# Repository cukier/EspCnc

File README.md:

# EspCnc

Controlador ESP32 para uma fresadora CNC 3018/3020/3030-3035, baseado no
firmware [grbl_esp32](https://github.com/bdring/grbl_esp32) (Bart Dring) e no
[esquematico de referencia da buildlog.net](https://www.buildlog.net/blog/wp-content/uploads/2018/07/esp32_test_schem_v1.pdf).

O objetivo e substituir a controladora original da CNC 3035 (tipicamente
baseada em GRBL sobre Arduino/Atmega) por uma placa com ESP32, aproveitando
mais pinos, maior clock, Wi-Fi/Bluetooth e a arquitetura de I/O configuravel
que o grbl_esp32 introduziu.

Este repositorio contem dois projetos independentes:

- [`firmware/`](firmware/) - firmware para o ESP32, em **ESP-IDF** (nao
  Arduino/PlatformIO), inspirado na logica de interpretacao G-code e no
  planejador de movimento do grbl_esp32.
- [`hardware/`](hardware/) - projeto de placa em **KiCad**, com o
  esquematico e PCB da interface entre o ESP32 e os drivers de motor de
  passo, fins-de-curso, spindle/laser e demais perifericos da CNC 3035,
  usando o esquematico da buildlog.net como ponto de partida.
- [`doc/`](doc/) - documentacao de referencia, incluindo o esquematico da
  buildlog.net usado como base do projeto.

## Estrutura

```
EspCnc/
├── firmware/   # Projeto ESP-IDF
├── hardware/   # Projeto KiCad
└── doc/        # Documentacao de referencia (esquematico, etc.)
```

## Firmware (ESP-IDF)

Ver [firmware/README.md](firmware/README.md).

## Hardware (KiCad)

Ver [hardware/README.md](hardware/README.md).

## Referencias

- grbl_esp32 (Bart Dring): https://github.com/bdring/grbl_esp32
- Esquematico ESP32 CNC (buildlog.net): https://www.buildlog.net/blog/wp-content/uploads/2018/07/esp32_test_schem_v1.pdf
- GRBL original: https://github.com/gnea/grbl

## Licenca

Distribuido sob a licenca MIT. Veja [LICENSE](LICENSE).

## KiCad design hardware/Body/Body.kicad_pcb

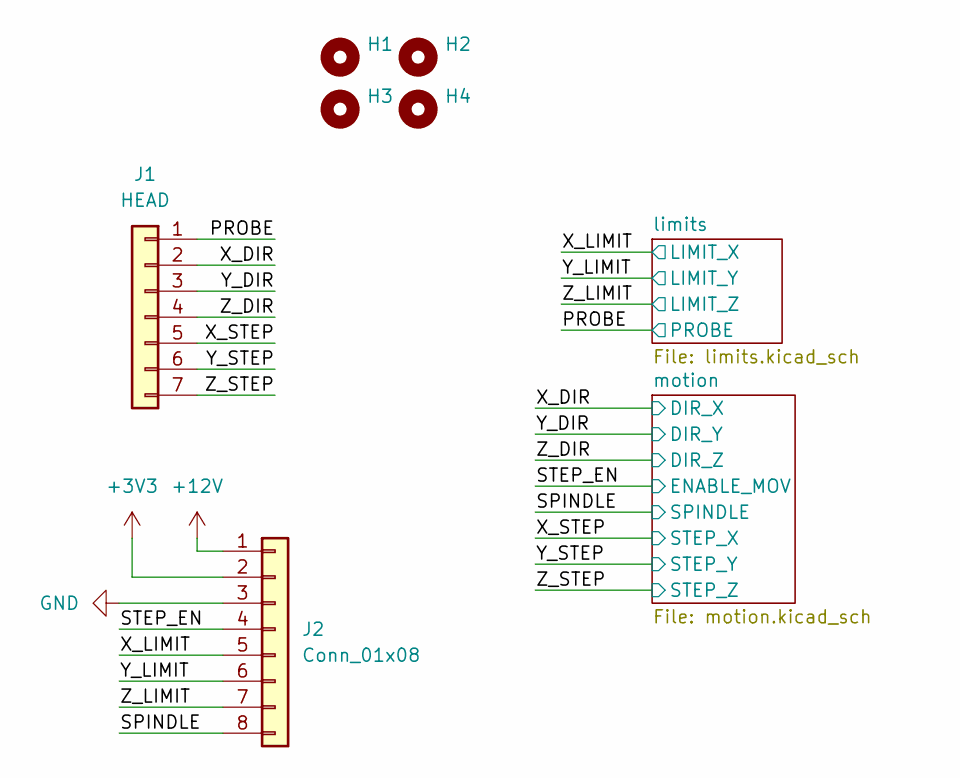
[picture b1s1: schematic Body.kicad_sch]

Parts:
H1, H2, H3, H4: MountingHole; MountingHole_3.5mm
J1: HEAD; PinSocket_1x07_P2.54mm_Vertical
J2: Conn_01x08; PinSocket_1x08_P2.54mm_Vertical

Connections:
+3V3: J2.2; also elsewhere on the board
+12V: J2.1; also elsewhere on the board
/PROBE: J1.1; also elsewhere on the board
/SPINDLE: J2.8; also elsewhere on the board
/STEP_EN: J2.4; also elsewhere on the board
/X_DIR: J1.2; also elsewhere on the board
/X_LIMIT: J2.5; also elsewhere on the board
/X_STEP: J1.5; also elsewhere on the board
/Y_DIR: J1.3; also elsewhere on the board
/Y_LIMIT: J2.6; also elsewhere on the board
/Y_STEP: J1.6; also elsewhere on the board
/Z_DIR: J1.4; also elsewhere on the board
/Z_LIMIT: J2.7; also elsewhere on the board
/Z_STEP: J1.7; also elsewhere on the board
GND: J2.3; also elsewhere on the board

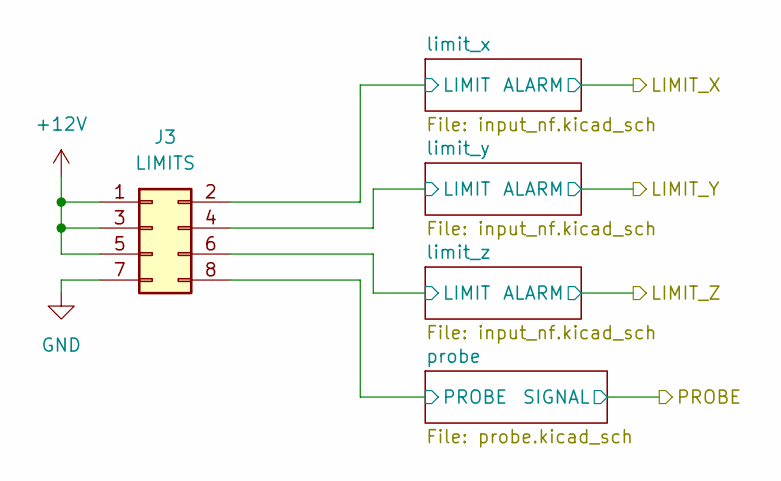
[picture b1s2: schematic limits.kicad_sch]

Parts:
J3: LIMITS; PinHeader_2x04_P2.54mm_Vertical

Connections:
+12V: J3.1, J3.3, J3.5; also elsewhere on the board
/limits/limit_x/LIMIT: J3.2; also elsewhere on the board
/limits/limit_y/LIMIT: J3.4; also elsewhere on the board
/limits/limit_z/LIMIT: J3.6; also elsewhere on the board
/limits/probe/PROBE: J3.8; also elsewhere on the board
GND: J3.7; also elsewhere on the board

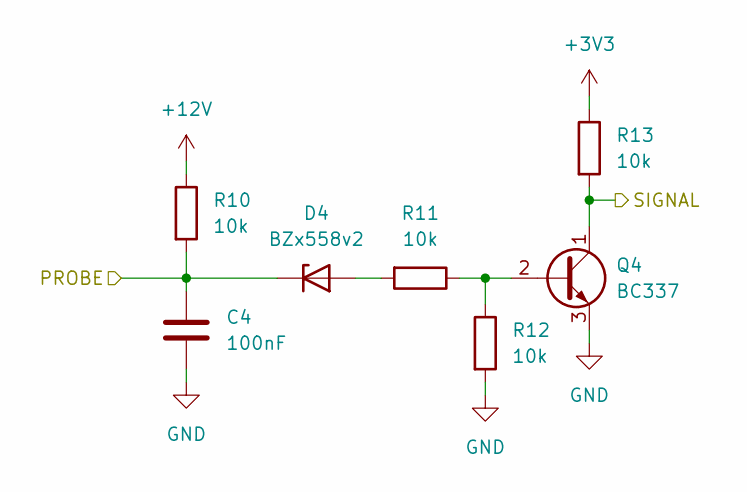
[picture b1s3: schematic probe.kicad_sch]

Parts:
C4: 100nF; C_1206_3216Metric_Pad1.33x1.80mm_HandSolder
D4: BZx558v2; D_MELF_Handsoldering
Q4: BC337; TO-92_Inline_Wide
R10, R11, R12, R13: 10k; R_1206_3216Metric_Pad1.30x1.75mm_HandSolder

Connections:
+3V3: R13.1; also elsewhere on the board
+12V: R10.1; also elsewhere on the board
/PROBE: Q4.1 (C), R13.2; also elsewhere on the board
/limits/probe/PROBE: C4.1, D4.1 (K), R10.2; also elsewhere on the board
GND: C4.2, Q4.3 (E), R12.2; also elsewhere on the board
unnamed: D4.2 (A), R11.2
unnamed: Q4.2 (B), R11.1, R12.1

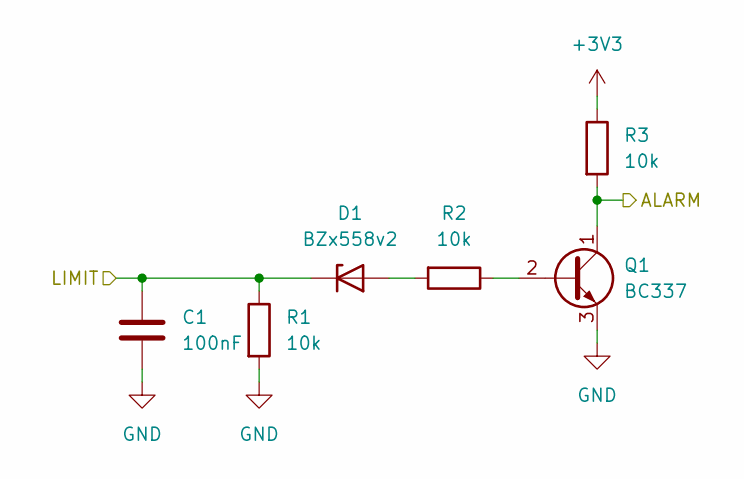
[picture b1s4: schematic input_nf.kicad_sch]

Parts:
C1: 100nF; C_1206_3216Metric_Pad1.33x1.80mm_HandSolder
D1: BZx558v2; D_MELF_Handsoldering
Q1: BC337; TO-92_Inline_Wide
R1, R2, R3: 10k; R_1206_3216Metric_Pad1.30x1.75mm_HandSolder

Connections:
+3V3: R3.1; also elsewhere on the board
/X_LIMIT: Q1.1 (C), R3.2; also elsewhere on the board
/limits/limit_x/LIMIT: C1.1, D1.1 (K), R1.1; also elsewhere on the board
GND: C1.2, Q1.3 (E), R1.2; also elsewhere on the board
unnamed: D1.2 (A), R2.2
unnamed: Q1.2 (B), R2.1

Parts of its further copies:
C2, C3: 100nF; C_1206_3216Metric_Pad1.33x1.80mm_HandSolder
D2, D3: BZx558v2; D_MELF_Handsoldering
Q2, Q3: BC337; TO-92_Inline_Wide
R4, R5, R6, R7, R8, R9: 10k; R_1206_3216Metric_Pad1.30x1.75mm_HandSolder

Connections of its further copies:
+3V3: R6.1, R9.1; also elsewhere on the board
/Y_LIMIT: Q2.1 (C), R6.2; also elsewhere on the board
/Z_LIMIT: Q3.1 (C), R9.2; also elsewhere on the board
/limits/limit_y/LIMIT: C2.1, D2.1 (K), R4.1; also elsewhere on the board
/limits/limit_z/LIMIT: C3.1, D3.1 (K), R7.1; also elsewhere on the board
GND: C2.2, C3.2, Q2.3 (E), Q3.3 (E), R4.2, R7.2; also elsewhere on the board
unnamed: D2.2 (A), R5.2
unnamed: D3.2 (A), R8.2
unnamed: Q2.2 (B), R5.1
unnamed: Q3.2 (B), R8.1

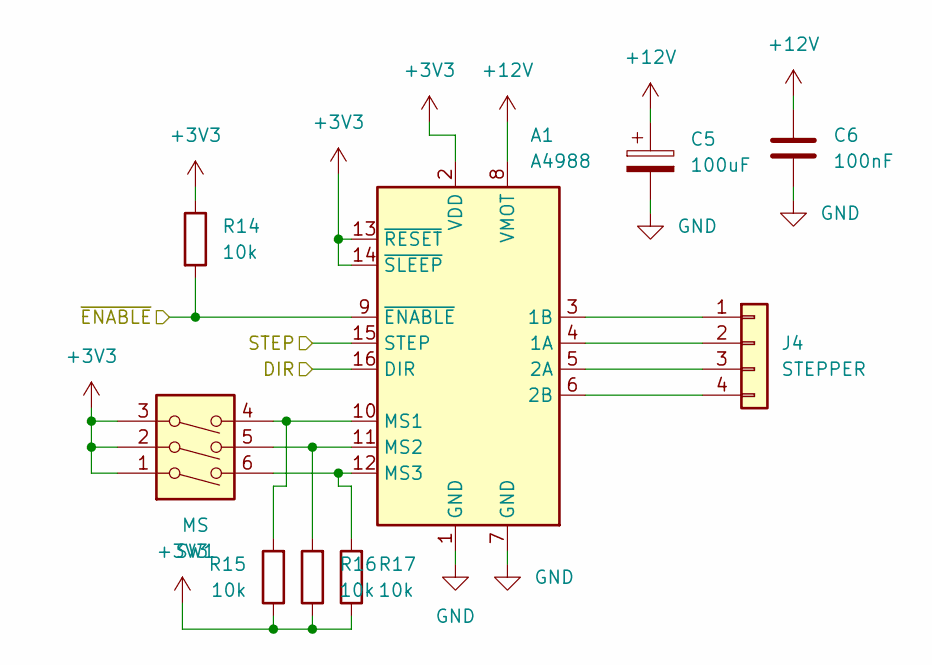
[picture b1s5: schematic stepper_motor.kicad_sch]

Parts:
A1: A4988; Pololu_Breakout-16_15.2x20.3mm
C5: 100uF; CP_Radial_D5.0mm_P2.50mm
C6: 100nF; C_1206_3216Metric_Pad1.33x1.80mm_HandSolder
J4: STEPPER; PinHeader_1x04_P2.54mm_Vertical
R14, R15, R16, R17: 10k; R_1206_3216Metric_Pad1.30x1.75mm_HandSolder
SW1: MS; SW_DIP_SPSTx03_Slide_6.7x9.18mm_W7.62mm_P2.54mm_LowProfile

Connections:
+3V3: A1.2 (VDD), A1.13 (~RESET), A1.14 (~SLEEP), R14.1, R15.1, R16.1, R17.1, SW1.1, SW1.2, SW1.3; also elsewhere on the board
+12V: A1.8 (VMOT), C5.1, C6.1; also elsewhere on the board
/STEP_EN: A1.9 (~ENABLE), R14.2; also elsewhere on the board
/X_DIR: A1.15 (STEP); also elsewhere on the board
/X_STEP: A1.16 (DIR); also elsewhere on the board
GND: A1.1 (GND), A1.7 (GND), C5.2, C6.2; also elsewhere on the board
unnamed: A1.4 (1A), J4.2
unnamed: A1.3 (1B), J4.1
unnamed: A1.5 (2A), J4.3
unnamed: A1.6 (2B), J4.4
unnamed: A1.10 (MS1), R15.2, SW1.4
unnamed: A1.11 (MS2), R16.2, SW1.5
unnamed: A1.12 (MS3), R17.2, SW1.6

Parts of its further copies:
A2, A3: A4988; Pololu_Breakout-16_15.2x20.3mm
C7, C9: 100uF; CP_Radial_D5.0mm_P2.50mm
C8, C10: 100nF; C_1206_3216Metric_Pad1.33x1.80mm_HandSolder
J5, J6: STEPPER; PinHeader_1x04_P2.54mm_Vertical
R18, R19, R20, R21, R22, R23, R24, R25: 10k; R_1206_3216Metric_Pad1.30x1.75mm_HandSolder
SW2, SW3: MS; SW_DIP_SPSTx03_Slide_6.7x9.18mm_W7.62mm_P2.54mm_LowProfile

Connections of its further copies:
+3V3: A2.2 (VDD), A2.13 (~RESET), A2.14 (~SLEEP), A3.2 (VDD), A3.13 (~RESET), A3.14 (~SLEEP), R18.1, R19.1, R20.1, R21.1, R22.1, R23.1, R24.1, R25.1, SW2.1, SW2.2, SW2.3, SW3.1, SW3.2, SW3.3; also elsewhere on the board
+12V: A2.8 (VMOT), A3.8 (VMOT), C7.1, C8.1, C9.1, C10.1; also elsewhere on the board
/STEP_EN: A2.9 (~ENABLE), A3.9 (~ENABLE), R18.2, R22.2; also elsewhere on the board
/Y_DIR: A2.15 (STEP); also elsewhere on the board
/Y_STEP: A2.16 (DIR); also elsewhere on the board
/Z_DIR: A3.15 (STEP); also elsewhere on the board
/Z_STEP: A3.16 (DIR); also elsewhere on the board
GND: A2.1 (GND), A2.7 (GND), A3.1 (GND), A3.7 (GND), C7.2, C8.2, C9.2, C10.2; also elsewhere on the board
unnamed: A2.4 (1A), J5.2
unnamed: A2.3 (1B), J5.1
unnamed: A2.5 (2A), J5.3
unnamed: A2.6 (2B), J5.4
unnamed: A2.10 (MS1), R19.2, SW2.4
unnamed: A2.11 (MS2), R20.2, SW2.5
unnamed: A2.12 (MS3), R21.2, SW2.6
unnamed: A3.4 (1A), J6.2
unnamed: A3.3 (1B), J6.1
unnamed: A3.5 (2A), J6.3
unnamed: A3.6 (2B), J6.4
unnamed: A3.10 (MS1), R23.2, SW3.4
unnamed: A3.11 (MS2), R24.2, SW3.5
unnamed: A3.12 (MS3), R25.2, SW3.6

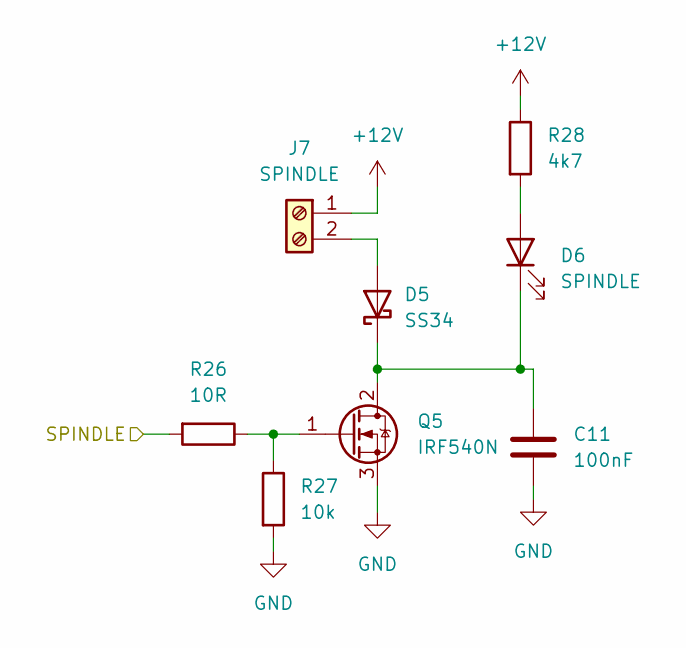
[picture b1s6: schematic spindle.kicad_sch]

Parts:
C11: 100nF; C_1206_3216Metric_Pad1.33x1.80mm_HandSolder
D5: SS34; D_SMA_Handsoldering
D6: SPINDLE; LED_D3.0mm
J7: SPINDLE; TerminalBlock_Phoenix_MKDS-1,5-2-5.08_1x02_P5.08mm_Horizont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
Q5: IRF540N; TO-220-3_Vertical
R26: 10R; R_1206_3216Metric_Pad1.30x1.75mm_HandSolder
R27: 10k; R_1206_3216Metric_Pad1.30x1.75mm_HandSolder
R28: 4k7; R_1206_3216Metric_Pad1.30x1.75mm_HandSolder

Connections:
+12V: J7.1, R28.1; also elsewhere on the board
/SPINDLE: R26.2; also elsewhere on the board
GND: C11.2, Q5.3 (S), R27.2; also elsewhere on the board
unnamed: D5.2 (A), J7.2
unnamed: C11.1, D5.1 (K), D6.1 (K), Q5.2 (D)
unnamed: D6.2 (A), R28.2
unnamed: Q5.1 (G), R26.1, R27.1

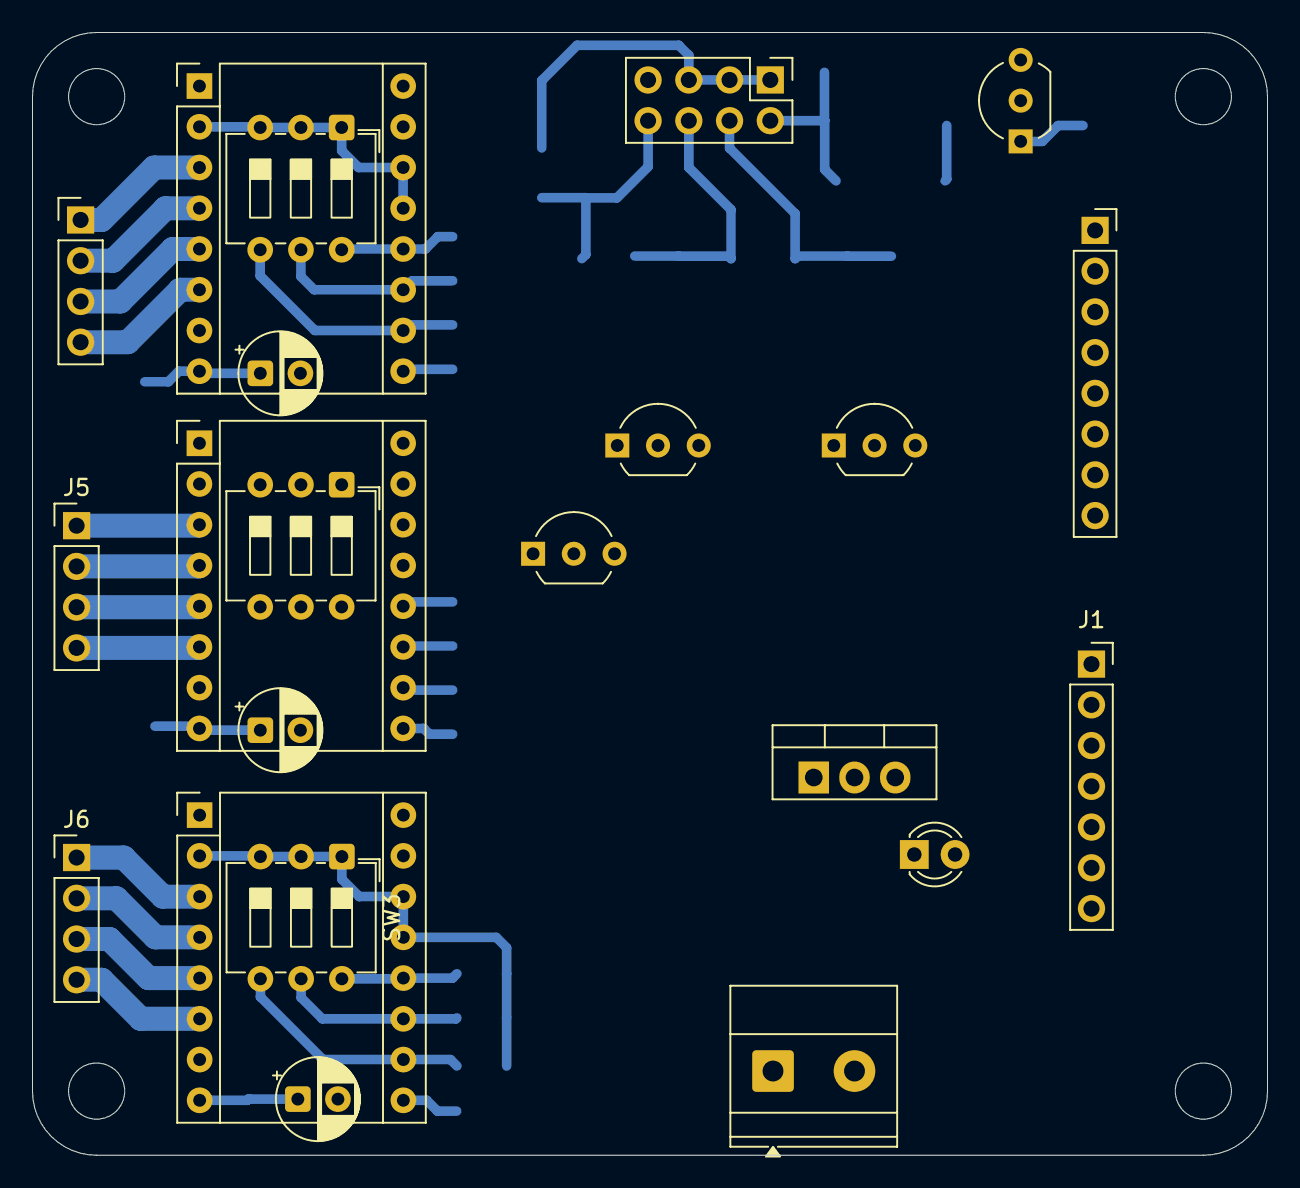
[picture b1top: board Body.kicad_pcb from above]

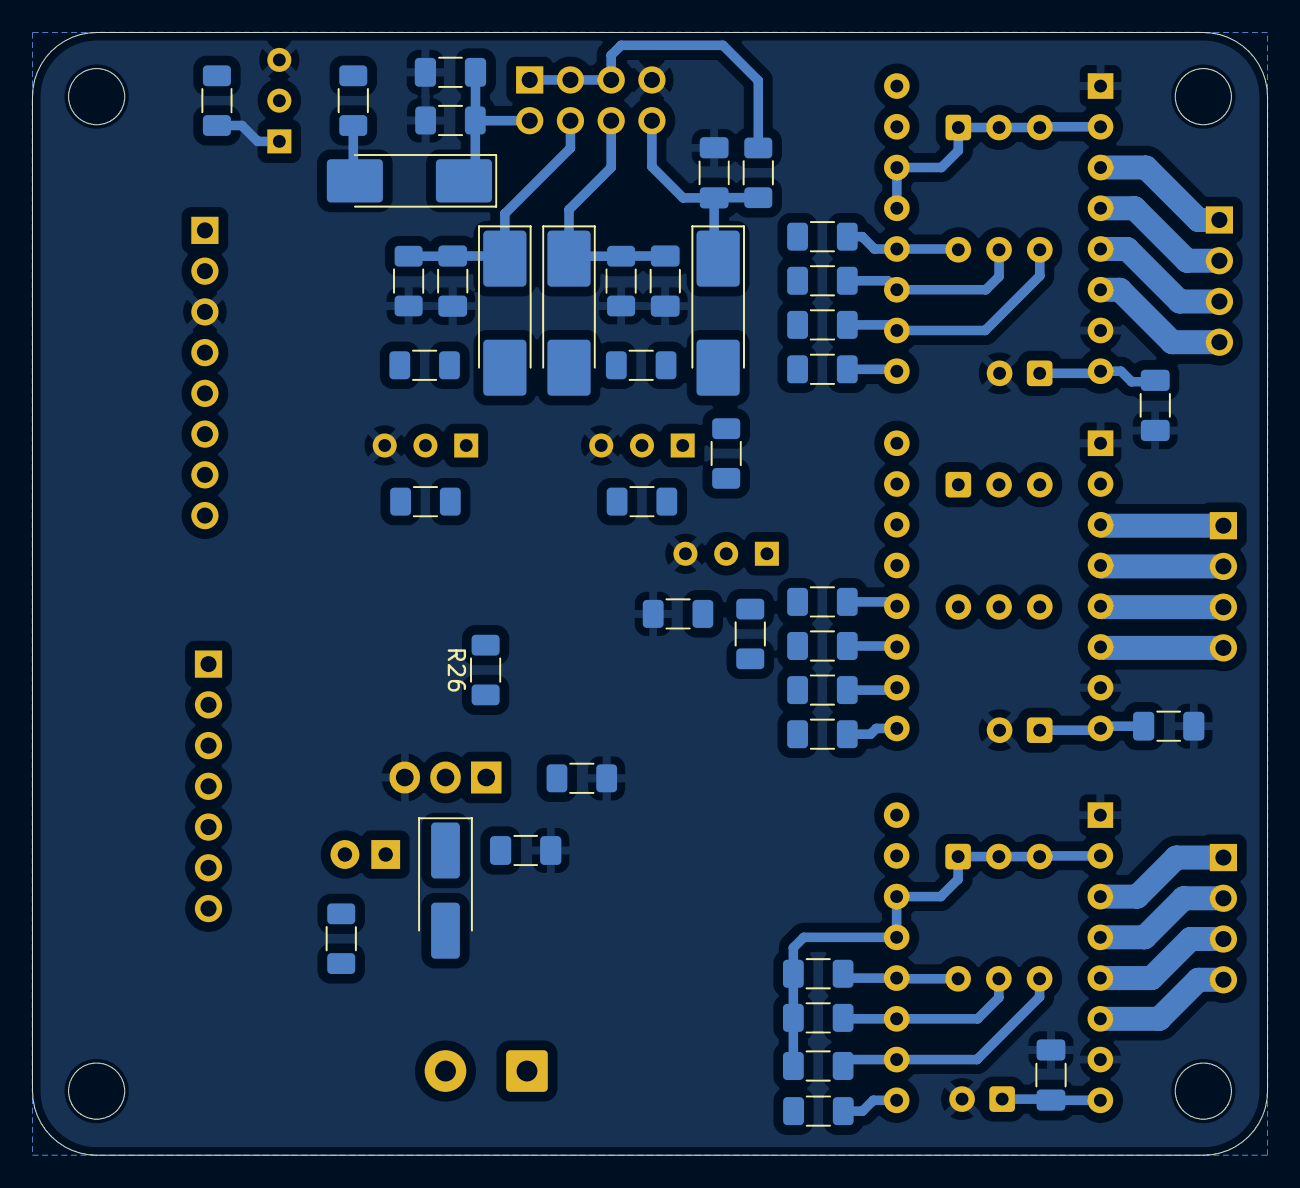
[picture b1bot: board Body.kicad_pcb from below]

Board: 2 copper layers, 77.0 x 70.0 mm, 67 parts (41 on the bottom side), 52 nets.

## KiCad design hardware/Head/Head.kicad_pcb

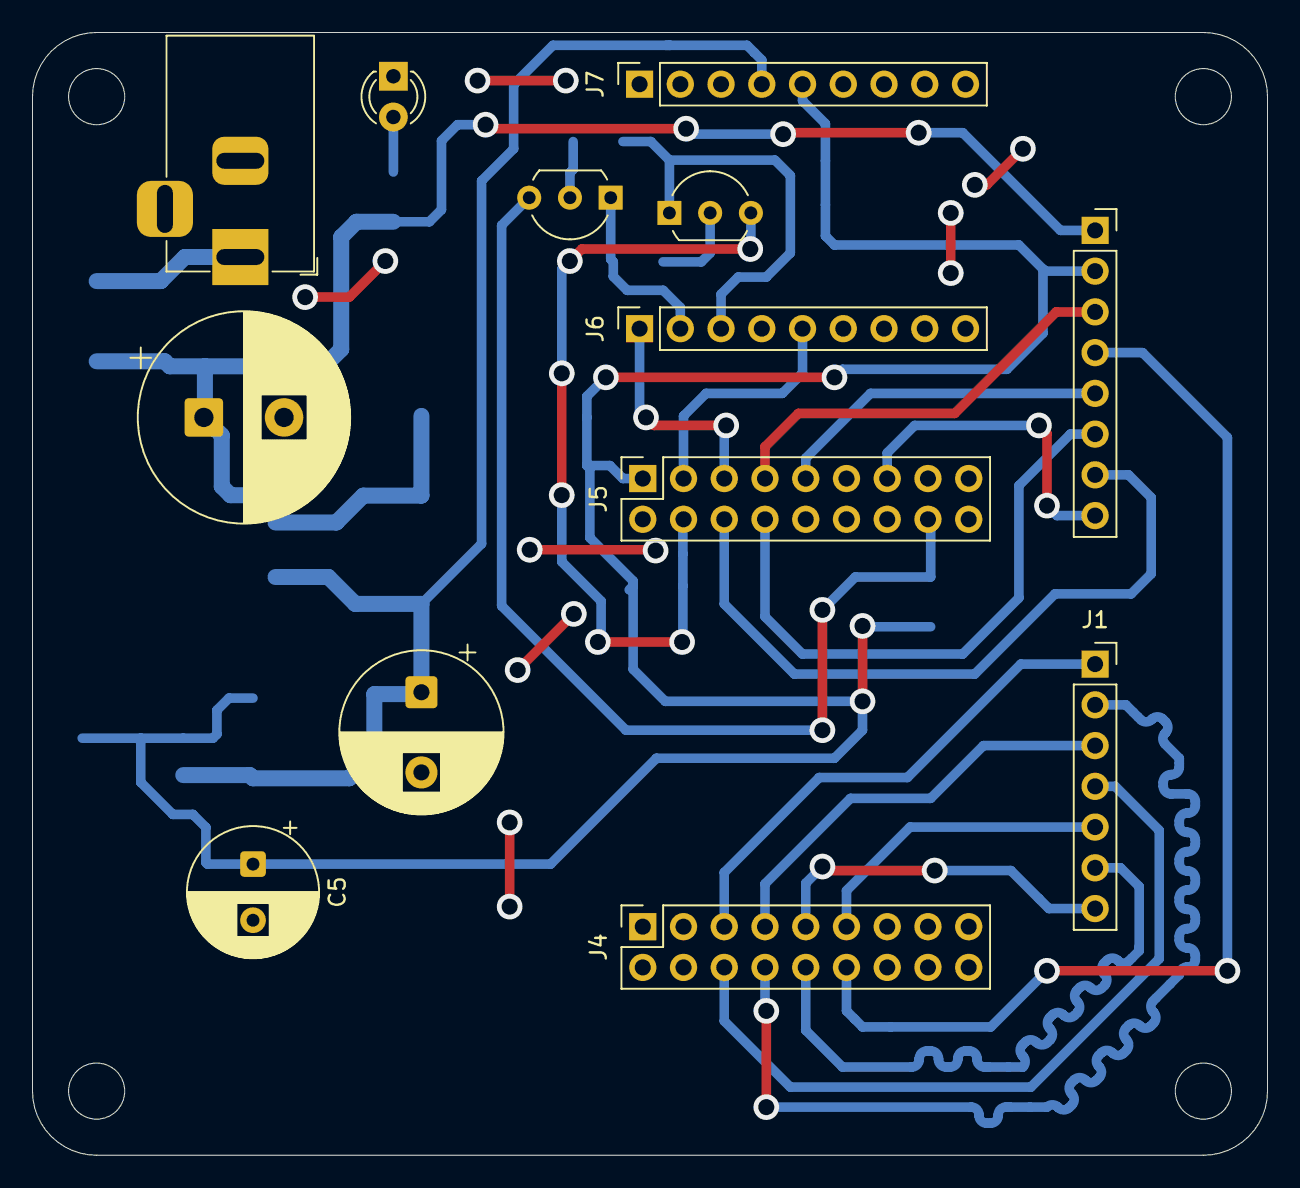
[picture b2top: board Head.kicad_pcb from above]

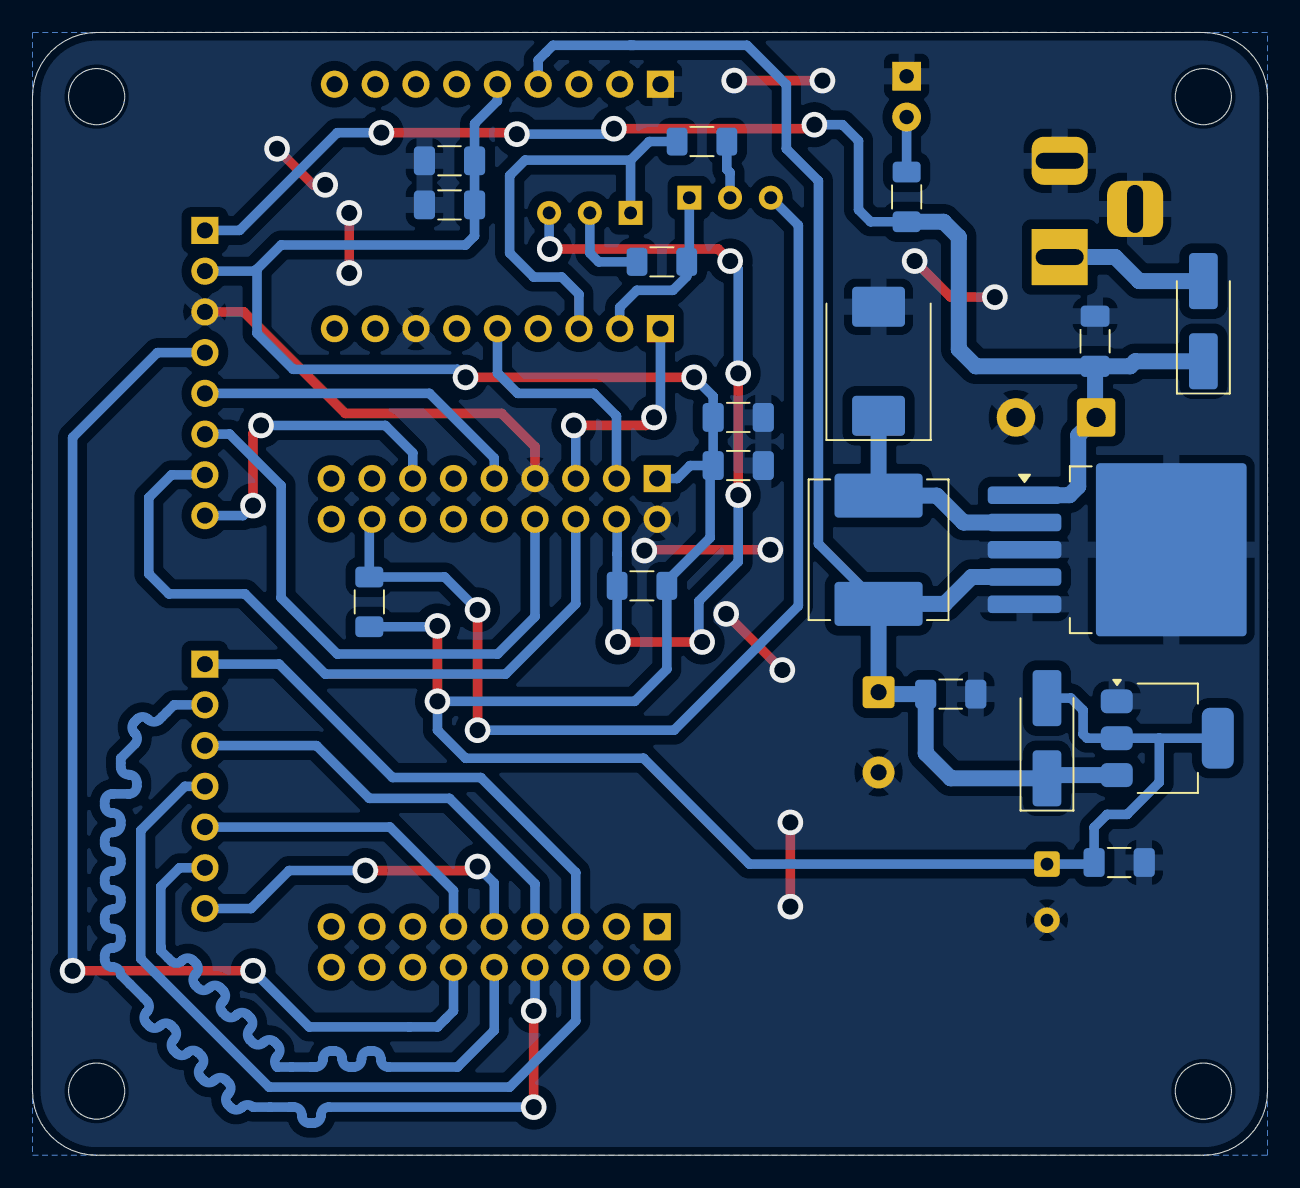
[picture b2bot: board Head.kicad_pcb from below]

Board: 2 copper layers, 77.0 x 70.0 mm, 35 parts (18 on the bottom side), 27 nets.

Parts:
C1: 470uF; CP_Radial_D13.0mm_P5.00mm
C2, C4, C6, C8, C10: 100nF; C_1206_3216Metric_Pad1.33x1.80mm_HandSolder
C3: 1000uF; CP_Radial_D10.0mm_P5.00mm
C5: 22uF; CP_Radial_D8.0mm_P3.50mm
C7, C9: 1uF; C_1206_3216Metric_Pad1.33x1.80mm_HandSolder
D1, D4: US1M; D_SMA_Handsoldering
D2: PWR; LED_D3.0mm
D3: B340; D_SMC
H1, H2, H3, H4: MountingHole; MountingHole_3.5mm
J1: HEAD; PinSocket_1x07_P2.54mm_Vertical
J2: Conn_01x08; PinSocket_1x08_P2.54mm_Vertical
J3: PWR; BarrelJack_Horizontal
J4, J5: ESP_32; PinSocket_2x09_P2.54mm_Vertical
J6: USB_E; PinSocket_1x09_P2.54mm_Vertical
J7: USB_D; PinSocket_1x09_P2.54mm_Vertical
L1: 100uH; L_Changjiang_FXL0840
Q1, Q2: PN2222A; TO-92L_Inline_Wide
R1, R2, R3, R4, R5: 10k; R_1206_3216Metric_Pad1.30x1.75mm_HandSolder
U1: LM2576HVS-5; TO-263-5_TabPin3
U2: AMS1117-3.3; SOT-223-3_TabPin2

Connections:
+3V3: C5.1, C6.1, C7.1, C8.1, C9.1, C10.1, D4.2 (A), J2.2, J5.1, J7.5, R3.2, R5.2, U2.2 (VO)
+5V: C3.1, C4.1, D4.1 (K), J7.4, L1.2, U1.4 (FB), U2.3 (VI)
+12V: C1.1, C2.1, D1.1 (K), J2.1, R1.1, U1.1 (VIN)
/BOOT: J5.16, Q2.3 (C), R5.1
/CH_PU: J5.4, Q1.3 (C), R3.1
/PROBE: J1.1, J4.5
/SPINDLE: J2.8, J5.13
/STEP_EN: J2.4, J4.12
/U0RX: J5.5, J6.1
/U0TX: J5.3, J6.5
/X_DIR: J1.2, J4.8
/X_LIMIT: J2.5, J5.9
/X_STEP: J1.5, J4.11
/Y_DIR: J1.3, J4.7
/Y_LIMIT: J2.6, J5.8
/Y_STEP: J1.6, J4.10
/Z_DIR: J1.4, J4.6
/Z_LIMIT: J2.7, J5.6
/Z_STEP: J1.7, J4.9
/usb/DTR: J6.2, Q2.1 (E), R2.2
/usb/RTS: J6.3, Q1.1 (E), R4.2
GND: C1.2, C2.2, C3.2, C4.2, C5.2, C6.2, C7.2, C8.2, C9.2, C10.2, D2.1 (K), D3.2 (A), J2.3, J3.2, J3.3, J5.2, J5.7, J6.7, J7.1, U1.3 (GND), U1.5 (~ON/OFF), U2.1 (GND)
unnamed: D1.2 (A), J3.1
unnamed: D2.2 (A), R1.2
unnamed: D3.1 (K), L1.1, U1.2 (OUT)
unnamed: Q1.2 (B), R2.1
unnamed: Q2.2 (B), R4.1

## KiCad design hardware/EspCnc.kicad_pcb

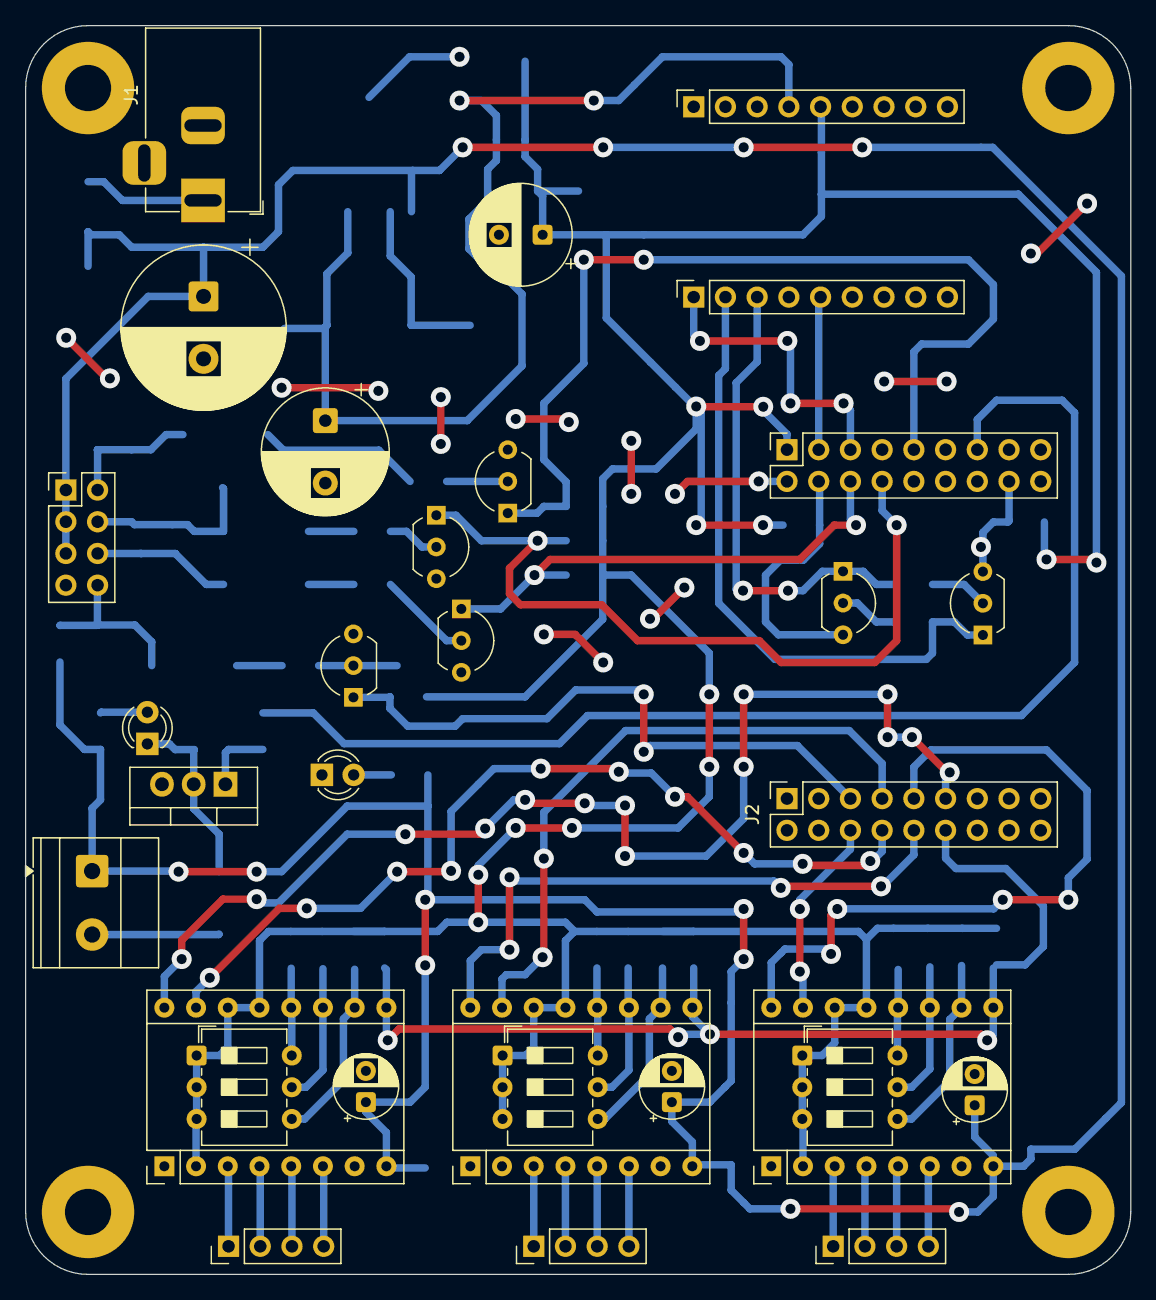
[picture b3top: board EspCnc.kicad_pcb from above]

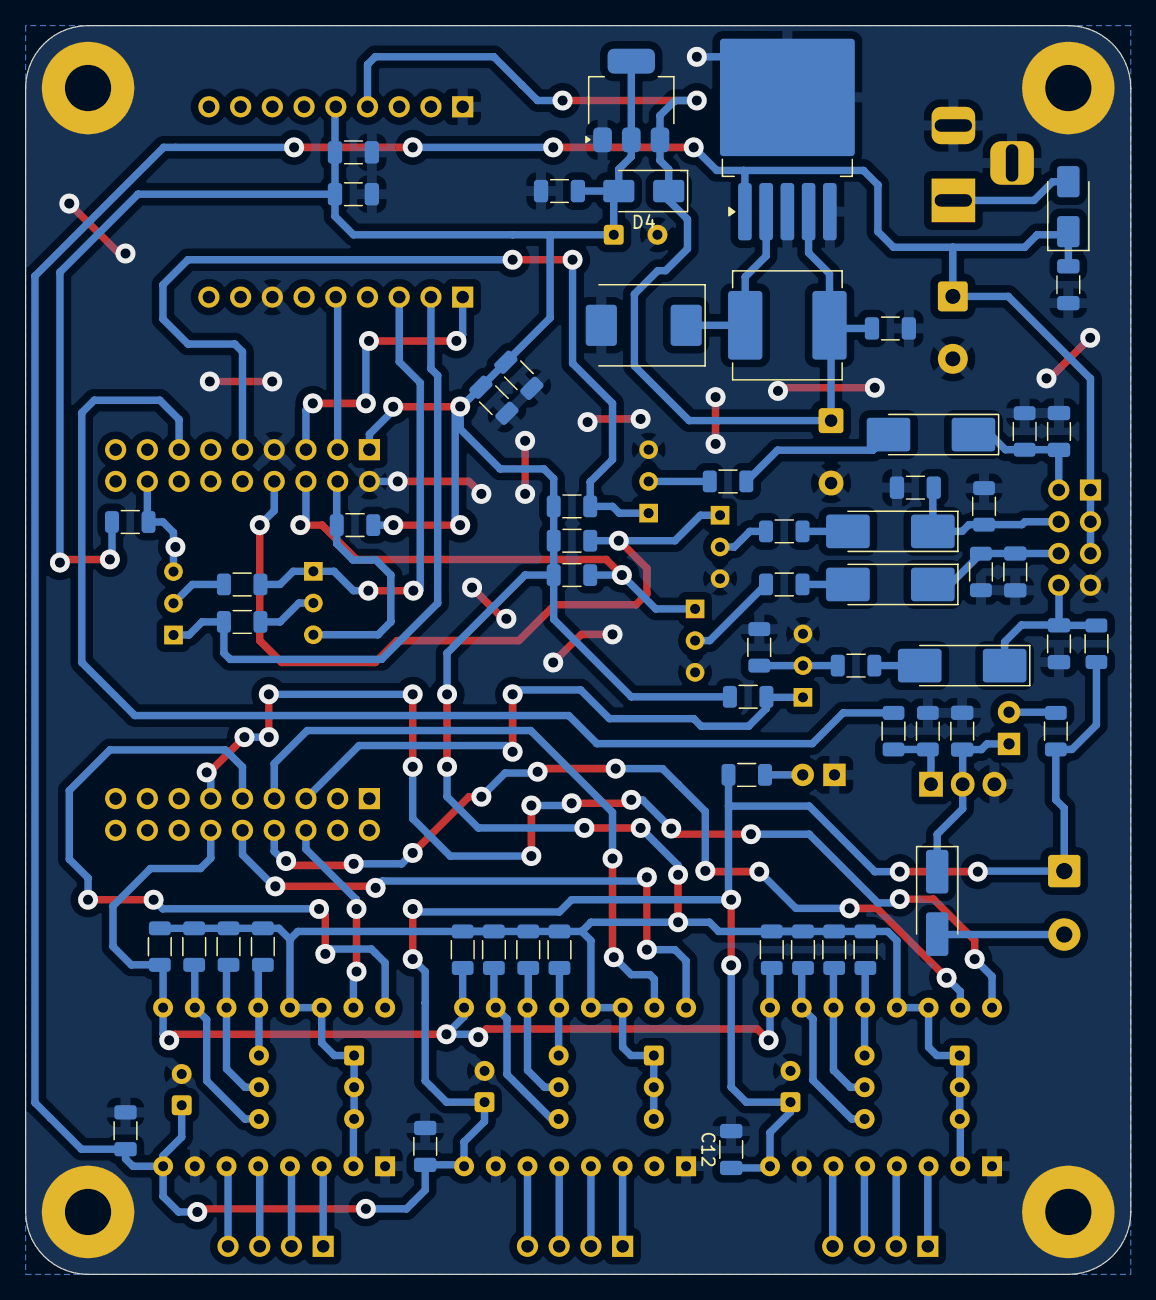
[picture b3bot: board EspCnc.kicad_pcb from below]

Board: 2 copper layers, 88.5 x 100.0 mm, 94 parts (59 on the bottom side), 64 nets.

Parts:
A1, A2, A3: A4988; Pololu_Breakout-16_15.2x20.3mm
C1: 470uF; CP_Radial_D13.0mm_P5.00mm
C2, C4, C6, C8, C10, C12, C14, C16, C17, C18, C19, C20, C21: 100nF; C_1206_3216Metric
C3: 1000uF; CP_Radial_D10.0mm_P5.00mm
C5: 22uF; CP_Radial_D8.0mm_P3.50mm
C7, C9: 1uF; C_1206_3216Metric
C11, C13, C15: 100uF; CP_Radial_D5.0mm_P2.50mm
D1, D4: US1M; D_SMA
D2: PWR; LED_D3.0mm
D3: B340; D_SMC
D5: SS34; D_SMA_Handsoldering
D6: SPINDLE; LED_D3.0mm
D7, D8, D9, D10: BZx558v2; D_MELF_Handsoldering
H1, H2, H3, H4: MountingHole_Pad; MountingHole_3.7mm_Pad
J1: PWR; BarrelJack_Horizontal
J2, J3: ESP_32; PinSocket_2x09_P2.54mm_Vertical
J4: USB_E; PinSocket_1x09_P2.54mm_Vertical
J5: USB_D; PinSocket_1x09_P2.54mm_Vertical
J6, J7, J8: STEPPER; PinHeader_1x04_P2.54mm_Vertical
J9: SPINDLE; TerminalBlock_Phoenix_MKDS-1,5-2-5.08_1x02_P5.08mm_Horizont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
J10: LIMITS; PinHeader_2x04_P2.54mm_Vertical
L1: 100uH; L_Changjiang_FXL0840
Q1, Q2: PN2222A; TO-92L_Inline_Wide
Q3: IRF540N; TO-220-3_Vertical
Q4, Q5, Q6, Q7: BC337; TO-92_Inline_Wide
R1, R2, R3, R4, R5, R6, R7, R8, R9, R10, R11, R12, R13, R14, R15, R16, R17, R19, R21, R22, R23, R24, R25, R26, R27, R28, R29, R30, R31, R32, R33: 10k; R_1206_3216Metric
R18: 10R; R_1206_3216Metric
R20: 4k7; R_1206_3216Metric
SW1, SW2, SW3: MS; SW_DIP_SPSTx03_Slide_6.7x9.18mm_W7.62mm_P2.54mm_LowProfile
U1: LM2576HVS-5; TO-263-5_TabPin3
U2: AMS1117-3.3; SOT-223-3_TabPin2

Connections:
+3V3: A1.2 (VDD), A1.13 (~RESET), A1.14 (~SLEEP), A2.2 (VDD), A2.13 (~RESET), A2.14 (~SLEEP), A3.2 (VDD), A3.13 (~RESET), A3.14 (~SLEEP), C5.1, C6.1, C7.1, C8.1, C9.1, C10.1, D4.2 (A), J3.1, J5.5, R3.2, R5.2, R6.1, R7.1, R8.1, R9.1, R10.1, R11.1, R12.1, R13.1, R14.1, R15.1, R16.1, R17.1, R23.1, R26.1, R29.1, R33.1, SW1.1, SW1.2, SW1.3, SW2.1, SW2.2, SW2.3, SW3.1, SW3.2, SW3.3, U2.2 (VO)
+5V: C3.1, C4.1, D4.1 (K), J5.4, L1.2, U1.4 (FB), U2.3 (VI)
+12V: A1.8 (VMOT), A2.8 (VMOT), A3.8 (VMOT), C1.1, C2.1, C11.1, C12.1, C13.1, C14.1, C15.1, C16.1, D1.1 (K), J9.1, J10.1, J10.3, J10.5, R1.1, R20.1, R30.1, U1.1 (VIN)
/BOOT: J3.16, Q2.3 (C), R5.1
/CHIP_PU: J3.4, Q1.3 (C), R3.1
/PROBE: J2.5, Q7.1 (C), R33.2
/SPINDLE: J3.13, R18.2
/STEP_ENABLE: A1.9 (~ENABLE), A2.9 (~ENABLE), A3.9 (~ENABLE), J2.12, R6.2, R10.2, R14.2
/U0RX: J3.5, J4.1
/U0TX: J3.3, J4.5
/X_DIR: A1.15 (STEP), J2.8
/X_LIMIT: J3.9, Q4.1 (C), R23.2
/X_STEP: A1.16 (DIR), J2.11
/Y_DIR: A2.15 (STEP), J2.7
/Y_LIMIT: J3.8, Q5.1 (C), R26.2
/Y_STEP: A2.16 (DIR), J2.10
/Z_DIR: A3.15 (STEP), J2.6
/Z_LIMIT: J3.6, Q6.1 (C), R29.2
/Z_STEP: A3.16 (DIR), J2.9
/limits/limit_x/LIMIT: C18.1, D7.1 (K), J10.2, R21.1
/limits/limit_y/LIMIT: C19.1, D8.1 (K), J10.4, R24.1
/limits/limit_z/LIMIT: C20.1, D9.1 (K), J10.6, R27.1
/limits/probe/PROBE: C21.1, D10.1 (K), J10.8, R30.2
/usb/DTR: J4.2, Q2.1 (E), R2.2
/usb/RTS: J4.3, Q1.1 (E), R4.2
GND: A1.1 (GND), A1.7 (GND), A2.1 (GND), A2.7 (GND), A3.1 (GND), A3.7 (GND), C1.2, C2.2, C3.2, C4.2, C5.2, C6.2, C7.2, C8.2, C9.2, C10.2, C11.2, C12.2, C13.2, C14.2, C15.2, C16.2, C17.2, C18.2, C19.2, C20.2, C21.2, D2.1 (K), D3.2 (A), H1.1, H2.1, H3.1, H4.1, J1.2, J1.3, J3.2, J3.7, J4.7, J5.1, J10.7, Q3.3 (S), Q4.3 (E), Q5.3 (E), Q6.3 (E), Q7.3 (E), R19.2, R21.2, R24.2, R27.2, R32.2, U1.3 (GND), U1.5 (~ON/OFF), U2.1 (GND)
unnamed: A1.4 (1A), J6.2
unnamed: A1.3 (1B), J6.1
unnamed: A1.5 (2A), J6.3
unnamed: A1.6 (2B), J6.4
unnamed: A1.10 (MS1), R7.2, SW1.4
unnamed: A1.11 (MS2), R8.2, SW1.5
unnamed: A1.12 (MS3), R9.2, SW1.6
unnamed: A2.4 (1A), J7.2
unnamed: A2.3 (1B), J7.1
unnamed: A2.5 (2A), J7.3
unnamed: A2.6 (2B), J7.4
unnamed: A2.10 (MS1), R11.2, SW2.4
unnamed: A2.11 (MS2), R12.2, SW2.5
unnamed: A2.12 (MS3), R13.2, SW2.6
unnamed: A3.4 (1A), J8.2
unnamed: A3.3 (1B), J8.1
unnamed: A3.5 (2A), J8.3
unnamed: A3.6 (2B), J8.4
unnamed: A3.10 (MS1), R15.2, SW3.4
unnamed: A3.11 (MS2), R16.2, SW3.5
unnamed: A3.12 (MS3), R17.2, SW3.6
unnamed: D1.2 (A), J1.1
unnamed: D2.2 (A), R1.2
unnamed: D3.1 (K), L1.1, U1.2 (OUT)
unnamed: D5.2 (A), J9.2
unnamed: C17.1, D5.1 (K), D6.1 (K), Q3.2 (D)
unnamed: D6.2 (A), R20.2
unnamed: D7.2 (A), R22.2
unnamed: D8.2 (A), R25.2
unnamed: D9.2 (A), R28.2
unnamed: D10.2 (A), R31.2
unnamed: Q1.2 (B), R2.1
unnamed: Q2.2 (B), R4.1
unnamed: Q3.1 (G), R18.1, R19.1
unnamed: Q4.2 (B), R22.1
unnamed: Q5.2 (B), R25.1
unnamed: Q6.2 (B), R28.1
unnamed: Q7.2 (B), R31.1, R32.1
